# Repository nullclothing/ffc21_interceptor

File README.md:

# FFC21 Interceptor

A sniffer/interceptor PCB for 21-pin FFC cables with 1mm pitch.
It was made while reverse engineering the interface for an Epson inkjet printhead.

### BOM

* 2 x Molex 200528-0210
* 1 x 21-pin 2.54mm pitch pin header
* 1 x 21-contact 1mm pitch FFC. Same-side contacts, such as [this](https://www.mouser.com/ProductDetail/Wurth-Elektronik/686621152001?qs=PhR8RmCirEYe0GLjOL%2FQVw%3D%3D&countrycode=US&currencycode=USD)

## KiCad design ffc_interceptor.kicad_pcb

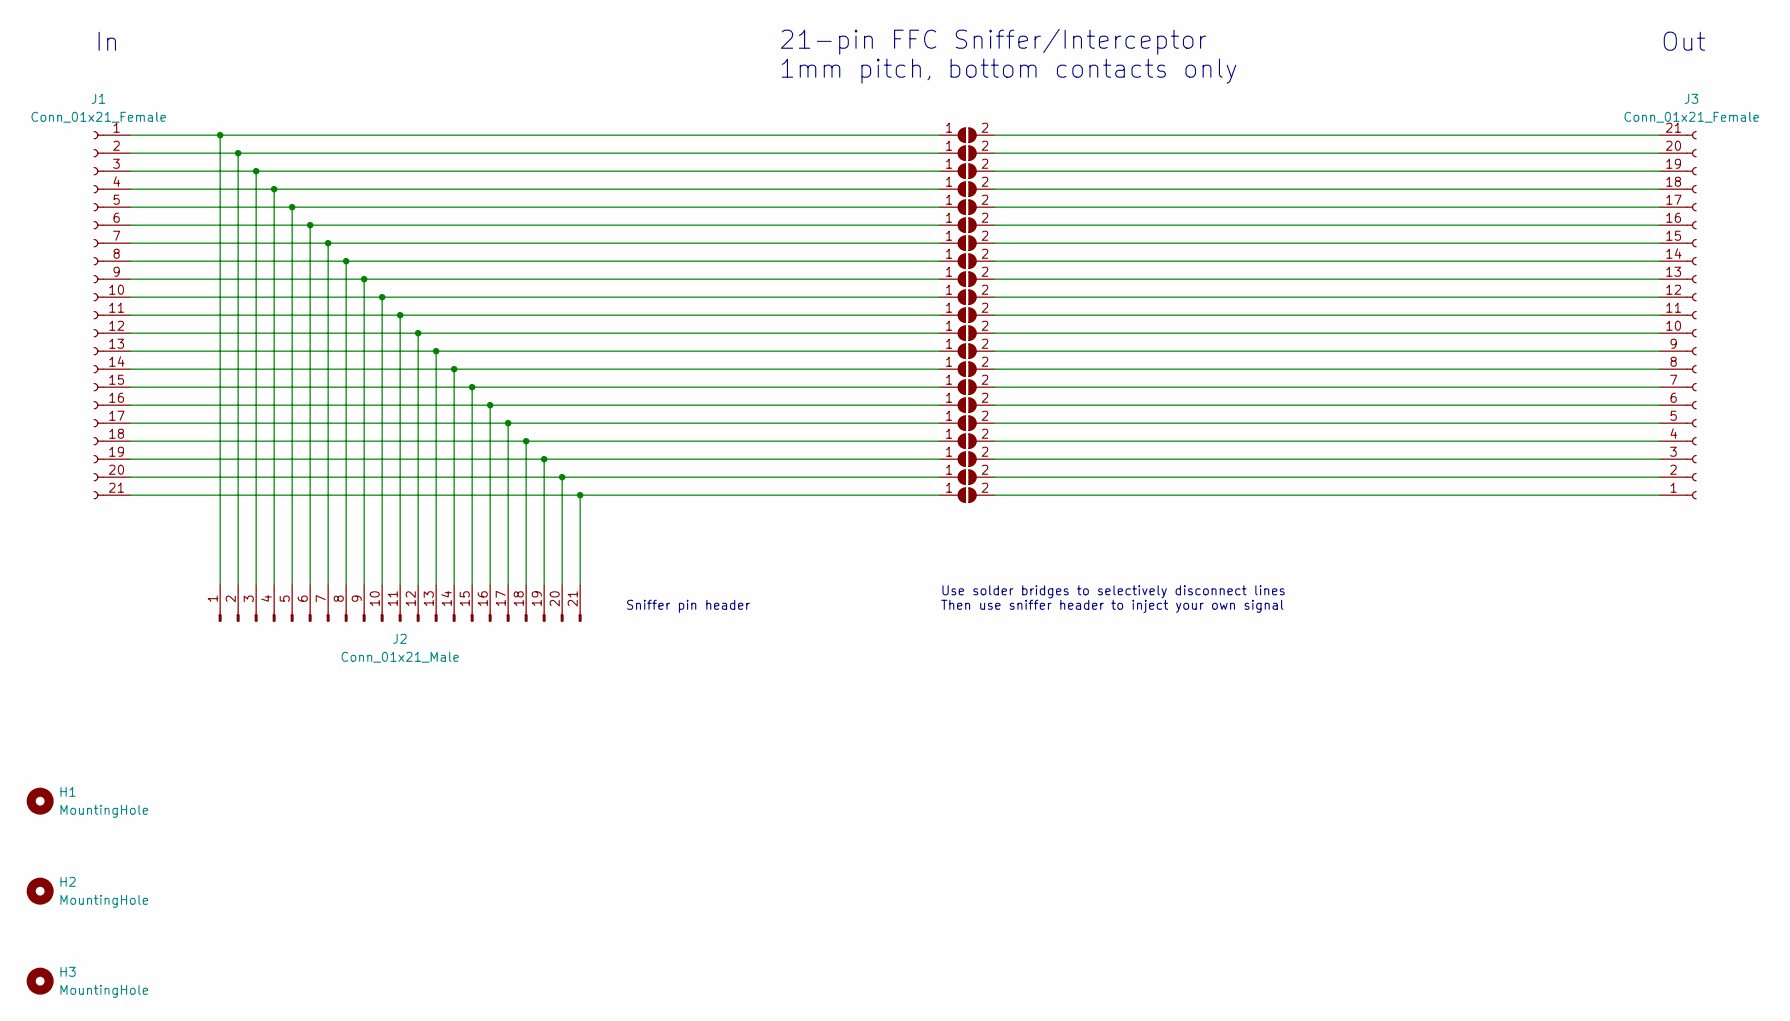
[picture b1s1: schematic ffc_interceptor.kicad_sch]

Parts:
H1, H2, H3: MountingHole; MountingHole_3.2mm_M3_DIN965_Pad_TopBottom
J1, J3: Conn_01x21_Female; Molex_200528-0210_1x21-1MP_P1.00mm_Horizontal
J2: Conn_01x21_Male; PinHeader_1x21_P2.54mm_Vertical
JP1, JP2, JP3, JP4, JP5, JP6, JP7, JP8, JP9, JP10, JP11, JP12, JP13, JP14, JP15, JP16, JP17, JP18, JP19, JP20, JP21: SolderJumper_2_Open; SolderJumper-2_P1.3mm_Open_TrianglePad1.0x1.5mm

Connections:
unnamed: J1.1, J2.1, JP1.1 (A)
unnamed: J3.21, JP1.2 (B)
unnamed: J1.2, J2.2, JP2.1 (A)
unnamed: J3.20, JP2.2 (B)
unnamed: J1.3, J2.3, JP3.1 (A)
unnamed: J3.19, JP3.2 (B)
unnamed: J1.4, J2.4, JP4.1 (A)
unnamed: J3.18, JP4.2 (B)
unnamed: J1.5, J2.5, JP5.1 (A)
unnamed: J3.17, JP5.2 (B)
unnamed: J1.6, J2.6, JP6.1 (A)
unnamed: J3.16, JP6.2 (B)
unnamed: J1.7, J2.7, JP7.1 (A)
unnamed: J3.15, JP7.2 (B)
unnamed: J1.8, J2.8, JP8.1 (A)
unnamed: J3.14, JP8.2 (B)
unnamed: J1.9, J2.9, JP9.1 (A)
unnamed: J3.13, JP9.2 (B)
unnamed: J1.10, J2.10, JP10.1 (A)
unnamed: J3.12, JP10.2 (B)
unnamed: J1.11, J2.11, JP11.1 (A)
unnamed: J3.11, JP11.2 (B)
unnamed: J1.12, J2.12, JP12.1 (A)
unnamed: J3.10, JP12.2 (B)
unnamed: J1.13, J2.13, JP13.1 (A)
unnamed: J3.9, JP13.2 (B)
unnamed: J1.14, J2.14, JP14.1 (A)
unnamed: J3.8, JP14.2 (B)
unnamed: J1.15, J2.15, JP15.1 (A)
unnamed: J3.7, JP15.2 (B)
unnamed: J1.16, J2.16, JP16.1 (A)
unnamed: J3.6, JP16.2 (B)
unnamed: J1.17, J2.17, JP17.1 (A)
unnamed: J3.5, JP17.2 (B)
unnamed: J1.18, J2.18, JP18.1 (A)
unnamed: J3.4, JP18.2 (B)
unnamed: J1.19, J2.19, JP19.1 (A)
unnamed: J3.3, JP19.2 (B)
unnamed: J1.20, J2.20, JP20.1 (A)
unnamed: J3.2, JP20.2 (B)
unnamed: J1.21, J2.21, JP21.1 (A)
unnamed: J3.1, JP21.2 (B)

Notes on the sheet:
21-pin FFC Sniffer/Interceptor 1mm pitch, bottom contacts only
Use solder bridges to selectively disconnect lines Then use sniffer header to inject your own signal
Out
Sniffer pin header

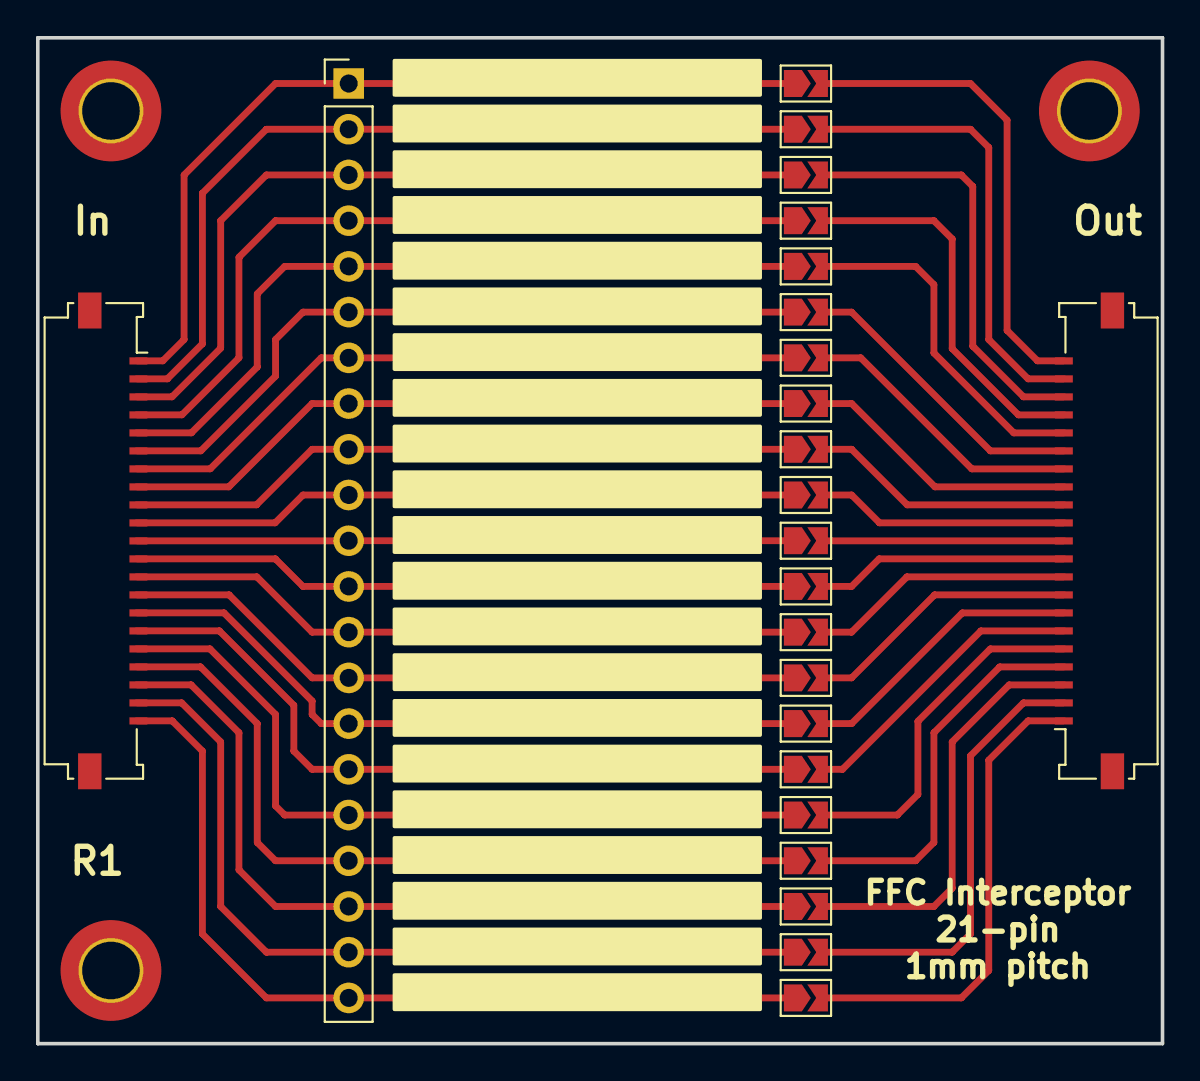
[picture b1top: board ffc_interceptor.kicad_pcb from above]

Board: 2 copper layers, 62.5 x 55.9 mm, 27 parts (0 on the bottom side), 42 nets.

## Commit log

2022-08-21 init
